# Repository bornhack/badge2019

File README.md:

# Bornhack Badge 2019

## About the hardware

Like the previous two years this years badge is again using the SiLabs Happy Gecko
microcontroller. This year it's sporting a 240x240 pixel screen with 6x6x6-bit colour
resolution, a MicroSD card reader and some basic IR communication.

We have separated the hardware design files from the code and put them in the
[hardware branch][hardware] for you to have a look at and build on.

You can download the microcontroller [reference manual][manual] and
[datasheet][] directly from [SiliconLabs][silabs].

[hardware]: https://github.com/bornhack/badge2019/tree/hardware
[silabs]: https://www.silabs.com/
[manual]: https://www.silabs.com/documents/public/reference-manuals/EFM32HG-RM.pdf
[datasheet]: https://www.silabs.com/documents/public/data-sheets/EFM32HG322.pdf

## About the code

This repo is meant as a starting point for developing your own code
for the Bornhack 2019 badge. Like the previous years we're using the
[geckonator][] library, but this year everything is split out
into separate source files. Every file ending in `.c` will
automatically be included in the build.

This way it should be easy to add your own code in a separate file
and add it to the main menu in `main.c`.
Have a look at `buttontest.c`, `showbmp.c` or `dumpir.c` for examples.

For reading the partition table and FAT filesystem on an SD-card we're using
the [FatFs][] library.

[FatFs]: http://elm-chan.org/fsw/ff/00index_e.html
[geckonator]: https://github.com/flummer/geckonator

## Hack your own badge

### 1. Install dependencies

##### Archlinux
```sh
pacman -S arm-none-eabi-gcc arm-none-eabi-newlib make
```

##### Debian/Ubuntu
```sh
apt-get install gcc-arm-none-eabi libnewlib-arm-none-eabi make
```

##### Fedora
```sh
dnf install arm-none-eabi-gcc arm-none-eabi-newlib make
```

##### NixOS/Nix
```sh
nix-shell
```

##### OSX

Download an arm-none-eabi toolchain from ARM [here][arm-toolchain].
Unpack the tarball and update your PATH variable to point to the unpacked `bin` directory.

##### Windows
###### Option 1
Download the apropriate installer from ARM [here][arm-toolchain].
Install it and update your path.
You'll also need GNU Make installed.
A pre-built version can be downloaded [here](http://gnuwin32.sourceforge.net/packages/make.htm).

###### Option 2

Use Windows Subsystem for Linux with Ubuntu 16.04 Xenial or newer and proceed as on Ubuntu above.

### 2. Get the source code

If you already have git installed
```
git clone https://github.com/bornhack/badge2019.git
cd badge2019
git submodule init
git submodule update
```

Otherwise you can download a tarball or zip file from
[https://github.com/bornhack/badge2019](https://github.com/bornhack/badge2019)

### 3. Build the code

Simply type `make` in the downloaded directory.
This should produce a file called `code.bin` in the `out` directory.

### 4. Update your badge

1. Connect a USB cable to the board and your computer.
2. Press the **BOOT** button on the badge (the red LED lights up).
3. Copy `out/code.bin` to the `GECKOBOOT` USB stick that appeared on your computer.
4. Eject (or unmount) the USB stick (the blue LED lights up), the badge reboots and you can watch your code run.

Alternatively if you have [dfu-utils][] installed step 3 and 4 can be replaced by typing
`make dfu` in the source repository.

[dfu-utils]: http://dfu-util.sourceforge.net/
[arm-toolchain]: https://developer.arm.com/open-source/gnu-toolchain/gnu-rm/downloads

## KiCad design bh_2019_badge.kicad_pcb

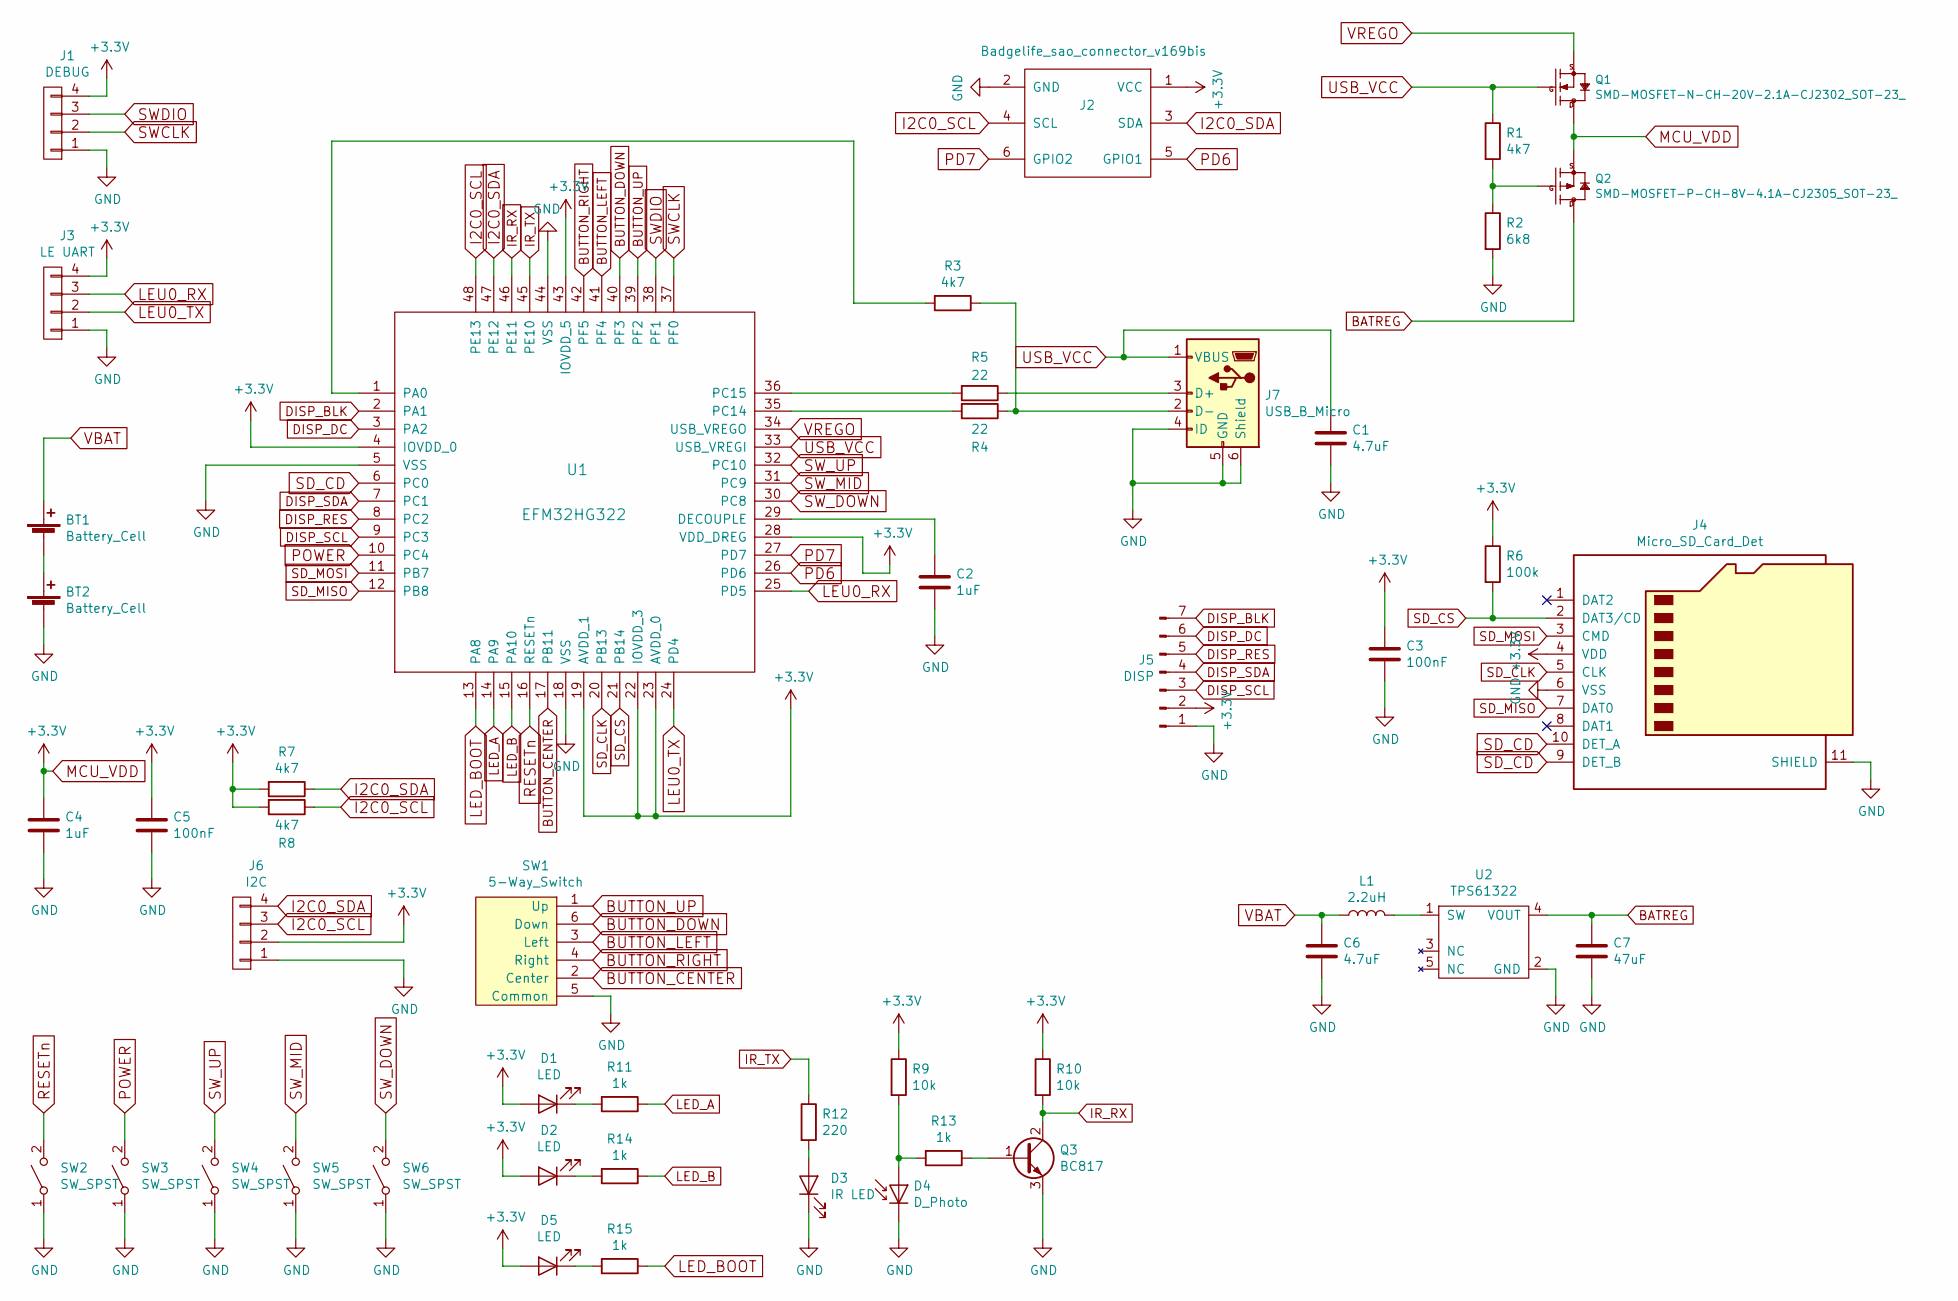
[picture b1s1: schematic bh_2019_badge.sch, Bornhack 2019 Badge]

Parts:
BT1, BT2: Battery_Cell; Single_AA_Holder_Sidemount
C1, C6: 4.7uF; C_0603
C2, C4: 1uF; C_0603
C3, C5: 100nF; C_0603
C7: 47uF; C_1210
D1, D2, D5: LED; LED_0603
D3: IR LED; IR_LED_1104_Side
D4: D_Photo; IR_LED_1104_Side
J1: DEBUG; Pin_Header_Straight_1x04_Pitch2.54mm
J2: Badgelife_sao_connector_v169bis; Badgelife-SAOv169-BADGE-2x3
J3: LE UART; Pin_Header_Straight_1x04_Pitch2.54mm
J4: Micro_SD_Card_Det; MEM2061
J5: DISP; Pin_Header_Straight_1x07_Pitch2.54mm
J6: I2C; Pin_Header_Straight_1x04_Pitch2.54mm
J7: USB_B_Micro; USB_Micro-B_10103594-0001LF
L1: 2.2uH; L_0805
Q1: SMD-MOSFET-N-CH-20V-2.1A-CJ2302_SOT-23_; SOT-23; MPN CJ2302
Q2: SMD-MOSFET-P-CH-8V-4.1A-CJ2305_SOT-23_; SOT-23; MPN CJ2305
Q3: BC817; SOT-23
R1, R3, R7, R8: 4k7; R_0603
R2: 6k8; R_0603
R4, R5: 22; R_0603
R6: 100k; R_0603
R9, R10: 10k; R_0603
R11, R13, R14, R15: 1k; R_0603
R12: 220; R_0603
SW1: 5-Way_Switch; SF303GJ26
SW2, SW3: SW_SPST; SW_SPST_PTS645
SW4, SW5, SW6: SW_SPST; Panasonic_EVQPUL_EVQPUC
U1: EFM32HG322; TQFP-48_7x7mm_Pitch0.5mm
U2: TPS61322; SOT-23-5

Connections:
BATREG: C7.1, Q2.3 (D), U2.4 (VOUT)
BUTTON_CENTER: SW1.2 (Center), U1.17 (PB11)
BUTTON_DOWN: SW1.6 (Down), U1.40 (PF3)
BUTTON_LEFT: SW1.3 (Left), U1.41 (PF4)
BUTTON_RIGHT: SW1.4 (Right), U1.42 (PF5)
BUTTON_UP: SW1.1 (Up), U1.39 (PF2)
DISP_BLK: J5.7, U1.2 (PA1)
DISP_DC: J5.6, U1.3 (PA2)
DISP_RES: J5.5, U1.8 (PC2)
DISP_SCL: J5.3, U1.9 (PC3)
DISP_SDA: J5.4, U1.7 (PC1)
GND: BT2.2 (-), C1.2, C2.2, C3.2, C4.2, C5.2, C6.2, C7.2, D3.1 (K), D4.1 (K), J1.1, J2.2 (GND), J3.1, J4.6 (VSS), J4.11 (SHIELD), J5.1, J6.1, J7.4 (ID), J7.5 (GND), J7.6 (Shield), Q3.3 (E), R2.2, SW1.5 (Common), SW1.SHIELD, SW2.1 (A), SW3.1 (A), SW4.1 (A), SW5.1 (A), SW6.1 (A), U1.5 (VSS), U1.18 (VSS), U1.44 (VSS), U2.2 (GND)
I2C0_SCL: J2.4 (SCL), J6.3, R8.1, U1.48 (PE13)
I2C0_SDA: J2.3 (SDA), J6.4, R7.1, U1.47 (PE12)
IR_RX: Q3.2 (C), R10.2, U1.46 (PE11)
IR_TX: R12.1, U1.45 (PE10)
LED_A: R11.1, U1.14 (PA9)
LED_B: R14.1, U1.15 (PA10)
LED_BOOT: R15.1, U1.13 (PA8)
LEU0_RX: J3.3, U1.25 (PD5)
LEU0_TX: J3.2, U1.24 (PD4)
MCU_VDD: C3.1, C4.1, C5.1, D1.2 (A), D2.2 (A), D5.2 (A), J1.4, J2.1 (VCC), J3.4, J4.4 (VDD), J5.2, J6.2, Q1.3 (D), Q2.2 (S), R6.1, R7.2, R8.2, R9.1, R10.1, U1.4 (IOVDD_0), U1.19 (AVDD_1), U1.22 (IOVDD_3), U1.23 (AVDD_0), U1.28 (VDD_DREG), U1.43 (IOVDD_5)
unnamed: BT1.2 (-), BT2.1 (+)
unnamed: C2.1, U1.29 (DECOUPLE)
unnamed: D1.1 (K), R11.2
unnamed: D2.1 (K), R14.2
unnamed: D3.2 (A), R12.2
unnamed: D4.2 (A), R9.2, R13.2
unnamed: D5.1 (K), R15.2
unnamed: J7.2 (D-), R3.1, R4.1
unnamed: J7.3 (D+), R5.1
unnamed: L1.2, U2.1 (SW)
unnamed: Q2.1 (G), R1.2, R2.1
unnamed: Q3.1 (B), R13.1
unnamed: R3.2, U1.1 (PA0)
unnamed: R4.2, U1.35 (PC14)
unnamed: R5.2, U1.36 (PC15)
PD6: J2.5 (GPIO1), U1.26 (PD6)
PD7: J2.6 (GPIO2), U1.27 (PD7)
POWER: SW3.2 (B), U1.10 (PC4)
RESETn: SW2.2 (B), U1.16 (RESETn)
SD_CD: J4.9 (DET_B), J4.10 (DET_A), U1.6 (PC0)
SD_CLK: J4.5 (CLK), U1.20 (PB13)
SD_CS: J4.2 (DAT3/CD), R6.2, U1.21 (PB14)
SD_MISO: J4.7 (DAT0), U1.12 (PB8)
SD_MOSI: J4.3 (CMD), U1.11 (PB7)
SWCLK: J1.2, U1.37 (PF0)
SWDIO: J1.3, U1.38 (PF1)
SW_DOWN: SW6.2 (B), U1.30 (PC8)
SW_MID: SW5.2 (B), U1.31 (PC9)
SW_UP: SW4.2 (B), U1.32 (PC10)
USB_VCC: C1.1, J7.1 (VBUS), Q1.1 (G), R1.1, U1.33 (USB_VREGI)
VBAT: BT1.1 (+), C6.1, L1.1
VREGO: Q1.2 (S), U1.34 (USB_VREGO)

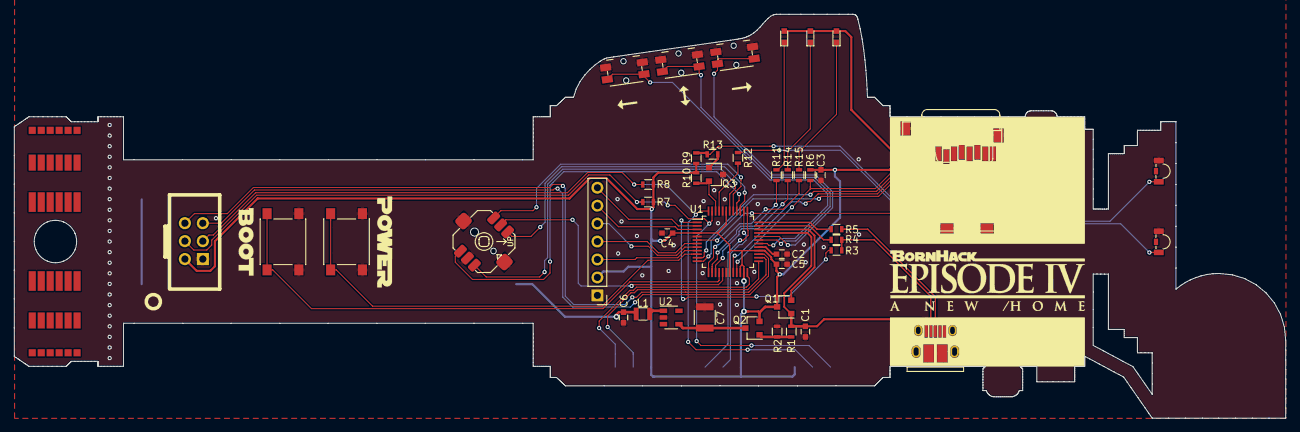
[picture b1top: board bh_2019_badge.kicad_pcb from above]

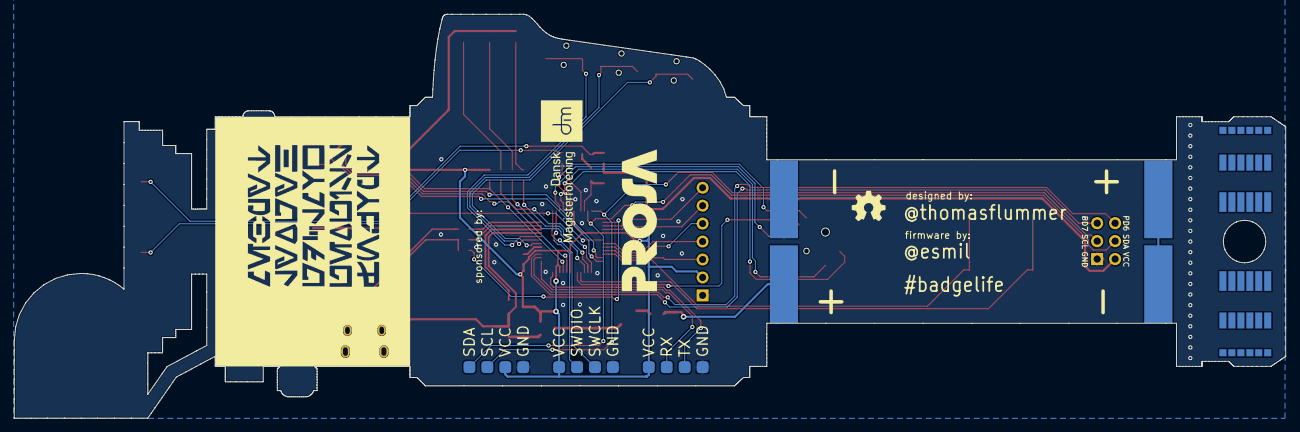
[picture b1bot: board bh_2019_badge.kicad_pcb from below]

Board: 2 copper layers, 180.0 x 57.2 mm, 48 parts (3 on the bottom side), 54 nets.

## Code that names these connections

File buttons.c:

/*
 * This file is part of badge2019.
 * Copyright 2019 Emil Renner Berthing <esmil@labitat.dk>
 *
 * badge2019 is free software: you can redistribute it and/or modify
 * it under the terms of the GNU General Public License as published by
 * the Free Software Foundation, either version 3 of the License, or
 * (at your option) any later version.
 *
 * badge2019 is distributed in the hope that it will be useful,
 * but WITHOUT ANY WARRANTY; without even the implied warranty of
 * MERCHANTABILITY or FITNESS FOR A PARTICULAR PURPOSE.  See the
 * GNU General Public License for more details.
 *
 * You should have received a copy of the GNU General Public License
 * along with badge2019. If not, see <http://www.gnu.org/licenses/>.
 */

#include <stdint.h>

#include "geckonator/gpio.h"

#include "timer.h"
#include "events.h"
#include "buttons.h"

#define POLL_RATE 50

static const gpio_pin_t buttonpin[BTN_MAX] = {
	[BTN_SUP]    = GPIO_PC10,
	[BTN_SMID]   = GPIO_PC9,
	[BTN_SDOWN]  = GPIO_PC8,
	[BTN_UP]     = GPIO_PF2,
	[BTN_DOWN]   = GPIO_PF3,
	[BTN_LEFT]   = GPIO_PF4,
	[BTN_RIGHT]  = GPIO_PF5,
	[BTN_CENTER] = GPIO_PB11,
	/* [BTN_POWER]    = GPIO_PC4, */
};

static const struct button_config *volatile buttonconfig;
static volatile uint8_t pressed;

struct button_state {
	struct timer_node n;
	uint16_t delay_left;
};

static struct button_state buttonstate[BTN_MAX];

static void
button_cb(struct timer_node *n)
{
	struct button_state *s = (struct button_state *)n;
	enum button btn = (enum button)(s - buttonstate);
	const struct button_config *c = &buttonconfig[btn];

	if (gpio_in(buttonpin[btn])) {
		if (c->release > 0)
			event_add(c->release);
		gpio_flag_clear(buttonpin[btn]);
		gpio_flag_enable(buttonpin[btn]);
		pressed -= 1;
	} else if (s->delay_left == 0) {
		if (c->repeat > 0)
			event_add(c->repeat);
		s->n.timeout += (c->rate > 0) ? c->rate : POLL_RATE;
		timer_add(&s->n);
	} else if (s->delay_left <= POLL_RATE) {
		s->delay_left = 0;
		if (c->longpress > 0)
			event_add(c->longpress);
		else if (c->repeat > 0)
			event_add(c->repeat);
		s->n.timeout += (c->rate > 0) ? c->rate : POLL_RATE;
		timer_add(&s->n);
	} else {
		s->delay_left -= POLL_RATE;
		s->n.timeout += (s->delay_left > POLL_RATE) ? POLL_RATE : s->delay_left;
		timer_add(&s->n);
	}
}

static void
button_click(enum button btn)
{
	const struct button_config *c;
	struct button_state *s;
	uint16_t delay;

	gpio_flag_disable(buttonpin[btn]);
	pressed += 1;

	c = &buttonconfig[btn];
	delay = (c->delay > 0) ? c->delay : POLL_RATE;

	s = &buttonstate[btn];
	s->delay_left = delay;
	s->n.timeout = timer_now();
	s->n.timeout += (delay > POLL_RATE) ? POLL_RATE : delay;
	timer_add(&s->n);
	if (c->press > 0)
		event_add(c->press);
}

void
GPIO_EVEN_IRQHandler(void)
{
	uint32_t flags = gpio_flags_enabled(gpio_flags());

	if (gpio_flag(flags, GPIO_PF2))
		button_click(BTN_UP);
	/*
	if (gpio_flag(flags, GPIO_PC4))
		button_click(BTN_POWER);
	*/
	if (gpio_flag(flags, GPIO_PF4))
		button_click(BTN_LEFT);
	if (gpio_flag(flags, GPIO_PC8))
		button_click(BTN_SDOWN);
	if (gpio_flag(flags, GPIO_PE10))
		button_click(BTN_SUP);
}

void
GPIO_ODD_IRQHandler(void)
{
	uint32_t flags = gpio_flags_enabled(gpio_flags());

	if (gpio_flag(flags, GPIO_PF3))
		button_click(BTN_DOWN);
	if (gpio_flag(flags, GPIO_PF5))
		button_click(BTN_RIGHT);
	if (gpio_flag(flags, GPIO_PC9))
		button_click(BTN_SMID);
	if (gpio_flag(flags, GPIO_PB11))
		button_click(BTN_CENTER);
}

void
buttons_init(const struct button_config config[BTN_MAX])
{
	unsigned int i;

	for (i = 0; i < BTN_MAX; i++) {
		gpio_pin_t pin = buttonpin[i];

		gpio_set(pin);
		gpio_mode(pin, GPIO_MODE_INPUTPULL);

		buttonstate[i].n.cb = button_cb;

		gpio_flag_select(pin);
		gpio_flag_falling_enable(pin);
		gpio_flag_clear(pin);
		gpio_flag_enable(pin);
	}

	/* init power button */
	gpio_set(GPIO_PC4);
	gpio_mode(GPIO_PC4, GPIO_MODE_INPUTPULL);

	buttonconfig = config;

	NVIC_SetPriority(GPIO_EVEN_IRQn, 3);
	NVIC_SetPriority(GPIO_ODD_IRQn, 3);
	NVIC_EnableIRQ(GPIO_EVEN_IRQn);
	NVIC_EnableIRQ(GPIO_ODD_IRQn);
}

void
buttons_uninit(void)
{
	unsigned int i;

	/* disable button gpio */
	for (i = 0; i < BTN_MAX; i++) {
		gpio_pin_t pin = buttonpin[i];

		gpio_flag_disable(pin);
		gpio_mode(pin, GPIO_MODE_DISABLED);
	}

	/* wait for button callbacks to complete */
	while (pressed > 0)
		__WFI();
}

void
buttons_config(const struct button_config config[BTN_MAX])
{
	while (1) {
		__disable_irq();
		if (pressed == 0)
			break;
		__enable_irq();
		__WFI();
	}
	events_clear();
	buttonconfig = config;
	__enable_irq();
}

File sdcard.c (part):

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#include "geckonator/gpio.h"
#include "geckonator/usart0.h"

#define SD_CD   GPIO_PC0
#define SD_CLK  GPIO_PB13
#define SD_CS   GPIO_PB14
#define SD_MISO GPIO_PB8
#define SD_MOSI GPIO_PB7

#define SD_CLOCKDIV_INIT 7488 /* 24MHz / (2 * (1 + 7488/256)) < 400kHz */
#define SD_CLOCKDIV_RUN     0 /* 24MHz / (2 * (1 +    0/256)) =  12MHz */
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void
sd_init(void)
{
	gpio_set(SD_CD);
	gpio_set(SD_CLK);
	gpio_set(SD_CS);
	gpio_set(SD_MOSI);
	gpio_set(SD_MISO);
	gpio_mode(SD_CD,   GPIO_MODE_INPUT);
	gpio_mode(SD_CLK,  GPIO_MODE_PUSHPULL);
	gpio_mode(SD_CS,   GPIO_MODE_WIREDAND);
	gpio_mode(SD_MISO, GPIO_MODE_INPUTPULL);
	gpio_mode(SD_MOSI, GPIO_MODE_PUSHPULL);

	clock_usart0_enable();
	/* location4:
	 * clk -> PB13 -> SD_CLK
	 * cs  -> PB14 -> SD_CS
	 * rx  -> PB8  -> SD_MISO
	 * tx  -> PB7  -> SD_MOSI
	 */
	usart0_config(USART_CTRL_MSBF
			| USART_CTRL_SYNC);
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{
	usart0_tx_enable();
	usart0_pins(0);
	gpio_mode(SD_CD,   GPIO_MODE_DISABLED);
	gpio_mode(SD_CLK,  GPIO_MODE_DISABLED);
	gpio_mode(SD_CS,   GPIO_MODE_DISABLED);
	gpio_mode(SD_MISO, GPIO_MODE_DISABLED);
	gpio_mode(SD_MOSI, GPIO_MODE_DISABLED);
	clock_usart0_disable();
}

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{
	uint8_t ret;

	gpio_clear(SD_CS);
	ret = sd__cmd(cmd, response, len);
	while (!usart0_tx_complete())
		/* wait */;
	gpio_set(SD_CS);
	return ret;
}

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	block_addressing = false;
	usart0_clock_div(SD_CLOCKDIV_INIT);

	gpio_clear(SD_CS);

	/* send 80 (at least 75) dummy bits */
	for (i = 10; i > 0; i--) {
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out:
	while (!usart0_tx_complete())
		/* wait */;
	gpio_set(SD_CS);
	usart0_clock_div(SD_CLOCKDIV_RUN);
	return ret;
}
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	unsigned int i;
	uint8_t ret;

	gpio_clear(SD_CS);

	usart0_txdata(0xFF);
	for (i = 0; i < 5; i++) {
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	usart0_rx_disable();
	while (!usart0_tx_complete())
		/* wait */;
	gpio_set(SD_CS);
	return ret;
}

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	cmd24[1] = lba & 0xFF;
	cmd24[0] = 0x58;

	gpio_clear(SD_CS);

	ret = sd__cmd(cmd24, NULL, 0);
	if (ret != 0x00) {
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	usart0_rx_disable();
	while (!usart0_tx_complete())
		/* wait */;
	gpio_set(SD_CS);
	return ret;
}

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
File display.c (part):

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#include "font.h"
#include "display.h"

#define DP_BLK GPIO_PA1 /* backlight */
#define DP_DC  GPIO_PA2 /* D/CX */
#define DP_SDA GPIO_PC1 /* data */
#define DP_RES GPIO_PC2 /* reset */
#define DP_SCL GPIO_PC3 /* clock */

/* spi max write clock rate 1/(66ns) = 15 MHz
 * spi max read clock rate 1/(150ns) = 6.6 MHz
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
	clock_usart1_enable();
	/* location5:
	 * clk -> PC3 -> DP_SCL (data latched on rising edge)
	 * cs  -> PC0 (not connected)
	 * rx  \  with USART_CTRL_LOOPBK enabled
	 * tx  -> PC1 -> DP_SDA
	 */
	usart1_config(USART_CTRL_MSBF
			| USART_CTRL_CLKPHA
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
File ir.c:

/*
 * This file is part of badge2019.
 * Copyright 2019 Emil Renner Berthing <esmil@labitat.dk>
 *
 * badge2019 is free software: you can redistribute it and/or modify
 * it under the terms of the GNU General Public License as published by
 * the Free Software Foundation, either version 3 of the License, or
 * (at your option) any later version.
 *
 * badge2019 is distributed in the hope that it will be useful,
 * but WITHOUT ANY WARRANTY; without even the implied warranty of
 * MERCHANTABILITY or FITNESS FOR A PARTICULAR PURPOSE.  See the
 * GNU General Public License for more details.
 *
 * You should have received a copy of the GNU General Public License
 * along with badge2019. If not, see <http://www.gnu.org/licenses/>.
 */

#include <stdint.h>
#include <stdbool.h>

#include "ir.h"

#include "geckonator/clock.h"
#include "geckonator/gpio.h"
#include "geckonator/usart0.h"

#define IR_RX GPIO_PE11
#define IR_TX GPIO_PE10

#define IR_CLOCKDIV 319744 /* 24MHz / (16 * (1 + 319744/256)) = 1200Hz */

/*
 * 24MHz / (2 * (1 + x/256)) = 9600Hz
 * 24MHz = 9600Hz * 2 * (1 + x/256)
 * 24MHz / (2 * 9600Hz) = 1 + x/256
 * (24MHz / 19200Hz - 1) * 256 = x
 */

#if 1
#include <stdio.h>
#define debug(...) printf(__VA_ARGS__)
#else
#define debug(...)
#endif

void
ir_init(void)
{
	gpio_clear(IR_RX);
	gpio_clear(IR_TX);
	gpio_mode(IR_RX, GPIO_MODE_INPUT);
	gpio_mode(IR_TX, GPIO_MODE_PUSHPULL);

	clock_usart0_enable();
	/* location0:
	 * rx -> PBE11 -> IR_RX
	 * tx -> PBE10 -> IR_TX
	 */
	usart0_config(USART_CTRL_TXINV | USART_CTRL_RXINV);
	usart0_frame_8n1();
	usart0_clock_div(IR_CLOCKDIV);
	usart0_tx_enable();
	usart0_rx_enable();
	usart0_pins(USART_ROUTE_LOCATION_LOC0
			| USART_ROUTE_TXPEN
			| USART_ROUTE_RXPEN);
}

void
ir_uninit(void)
{
	usart0_rxtx_enable();
	usart0_pins(0);
	gpio_mode(IR_RX, GPIO_MODE_DISABLED);
	gpio_mode(IR_TX, GPIO_MODE_DISABLED);
	clock_usart0_enable();
}

void
ir_send(uint8_t c)
{
	while (!usart0_tx_buffer_level())
		/* wait */;
	usart0_txdata(c);
}

int
ir_recv(void)
{
	if (!usart0_rx_valid())
		return -1;
	return usart0_rxdata();
}

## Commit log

2019-08-09 Update readme with instructions for git submodules, add nix file
2019-08-09 README: add instructions for git submodule
2019-08-09 README: add instructions and script for NixOS
2019-08-12 Add the classic Snake game
2019-08-12 fix indentation of b0rken editor
2019-08-12 program: update program data
2019-08-12 snake: add the classic Snake game
2019-08-12 snake: add variable resolution
2019-08-12 snake: cleanup
2019-08-12 display: pull backlight low on uninit
2019-08-25 Production version
2019-08-25 Added readme
2019-11-30 main: look for LOGO.BMP when idle
    ..and show that instead of the BornHack 2019 logo if found
2019-12-27 docs: added led colors that light up to README for badge update
2019-12-27 fix: batch to badge
2019-12-27 README: document LEDs that light when updating the badge
2020-08-18 font.h: fix missing extern declaration
    This is a real bug, but it only breaks on newer compilers.
